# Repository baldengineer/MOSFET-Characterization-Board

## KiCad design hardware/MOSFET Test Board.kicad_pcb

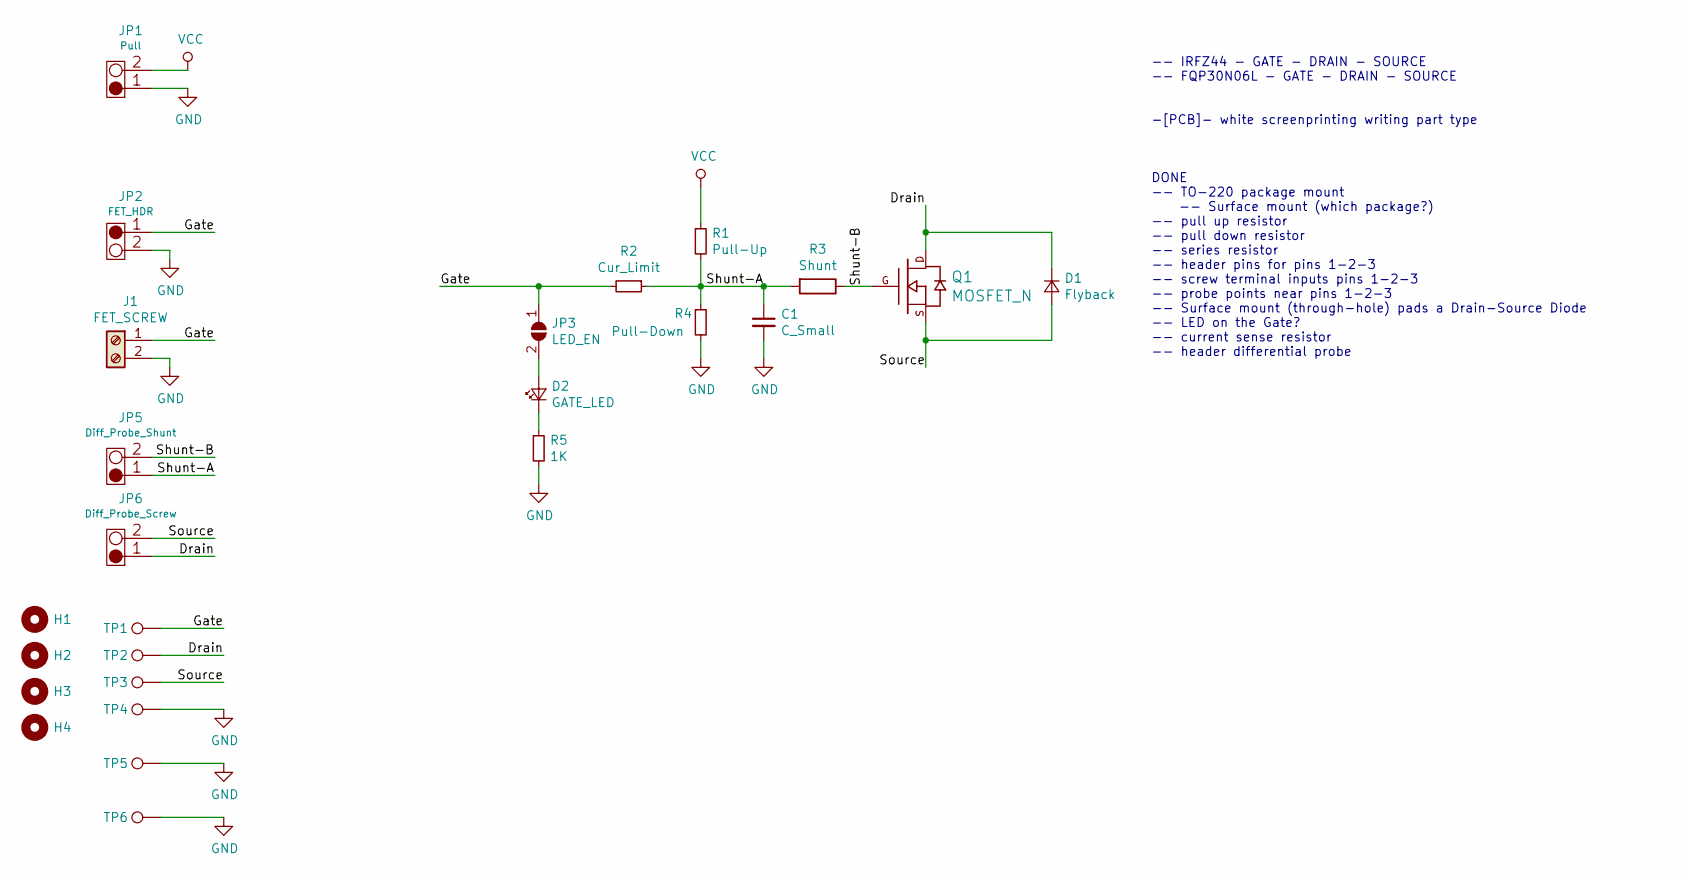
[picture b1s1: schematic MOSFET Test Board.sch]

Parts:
C1: C_Small; C_0805_2012Metric_Pad1.15x1.40mm_HandSolder
D1: Flyback; D_SOD-523
D2: GATE_LED; D_1206_3216Metric
H1, H2, H3, H4: MountingHole; MountingHole_2.7mm_M2.5
J1: FET_SCREW; TerminalBlock_Phoenix_MKDS-1,5-2-5.08_1x02_P5.08mm_Horizont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
JP1: Pull; PinHeader_1x02_P2.54mm_Vertical
JP2: FET_HDR; PinHeader_1x02_P2.54mm_Vertical
JP3: LED_EN; SolderJumper-2_P1.3mm_Open_Pad1.0x1.5mm
JP5: Diff_Probe_Shunt; TerminalBlock_bornier-2_P5.08mm
JP6: Diff_Probe_Screw; TerminalBlock_Phoenix_MKDS-1,5-2-5.08_1x02_P5.08mm_Horizont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
Q1: MOSFET_N; TO-220-3_Vertical_GDS
R1: Pull-Up; R_1206_3216Metric_Pad1.42x1.75mm_HandSolder
R2: Cur_Limit; R_1206_3216Metric_Pad1.42x1.75mm_HandSolder
R3: Shunt; R_2512_6332Metric_Pad1.52x3.35mm_HandSolder
R4: Pull-Down; R_1206_3216Metric_Pad1.42x1.75mm_HandSolder
R5: 1K; R_1206_3216Metric_Pad1.42x1.75mm_HandSolder
TP1, TP2, TP3, TP4, TP6: TestPoint; TestPoint_Loop_D2.50mm_Drill1.0mm
TP5: TestPoint-esden said I could; TestPoint_Loop_D2.50mm_Drill1.0mm

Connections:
/Drain: D1.1 (K), JP6.1, Q1.D, TP2.1
/Gate: J1.1, JP2.1, JP3.1 (A), R2.2, TP1.1
/Shunt-A: C1.1, JP5.1, R1.2, R2.1, R3.2, R4.1
/Shunt-B: JP5.2, Q1.G, R3.1
/Source: D1.2 (A), JP6.2, Q1.S, TP3.1
GND: C1.2, J1.2, JP1.1, JP2.2, R4.2, R5.2, TP4.1, TP5.1, TP6.1
unnamed: D2.1 (K), R5.1
unnamed: D2.2 (A), JP3.2 (B)
VCC: JP1.2, R1.1

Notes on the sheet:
-- IRFZ44 - GATE - DRAIN - SOURCE -- FQP30N06L - GATE - DRAIN - SOURCE -[PCB]- white screenprinting writing part type DONE -- TO-220 package mount -- Surface mount (which package?) -- pull up resistor -- pull down resistor -- series resistor -- header pins for pins 1-2-3 -- screw terminal inputs pi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

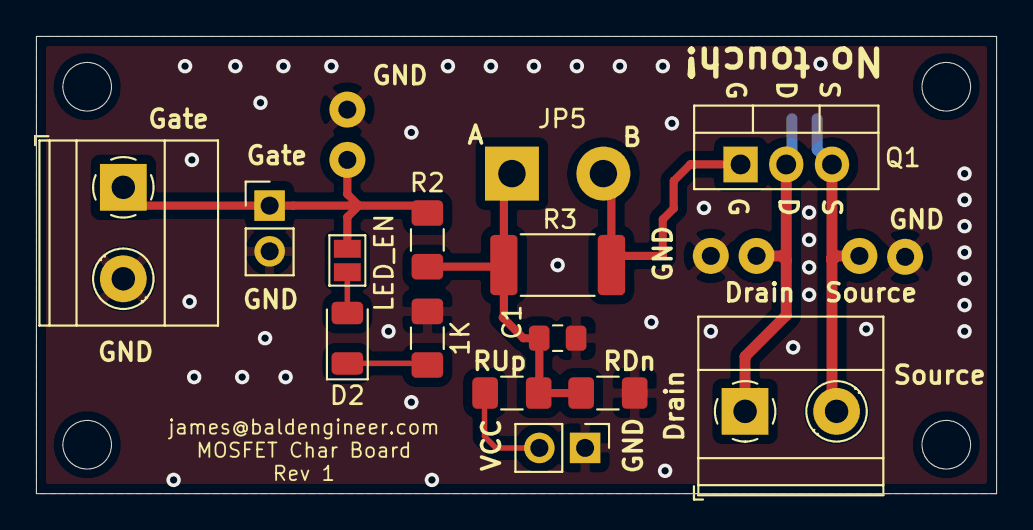
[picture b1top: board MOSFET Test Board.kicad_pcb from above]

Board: 2 copper layers, 53.3 x 25.4 mm, 25 parts (1 on the bottom side), 9 nets.
